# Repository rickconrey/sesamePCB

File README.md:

# Sesame PCB
The PCB for Sesame garage door opener

This PCB connects the [STM32F4Discovery](http://www.st.com/web/catalog/tools/FM116/SC959/SS1532/PF252419) board to the sparkfun [RN-52 breakout board](https://www.sparkfun.com/products/12849).

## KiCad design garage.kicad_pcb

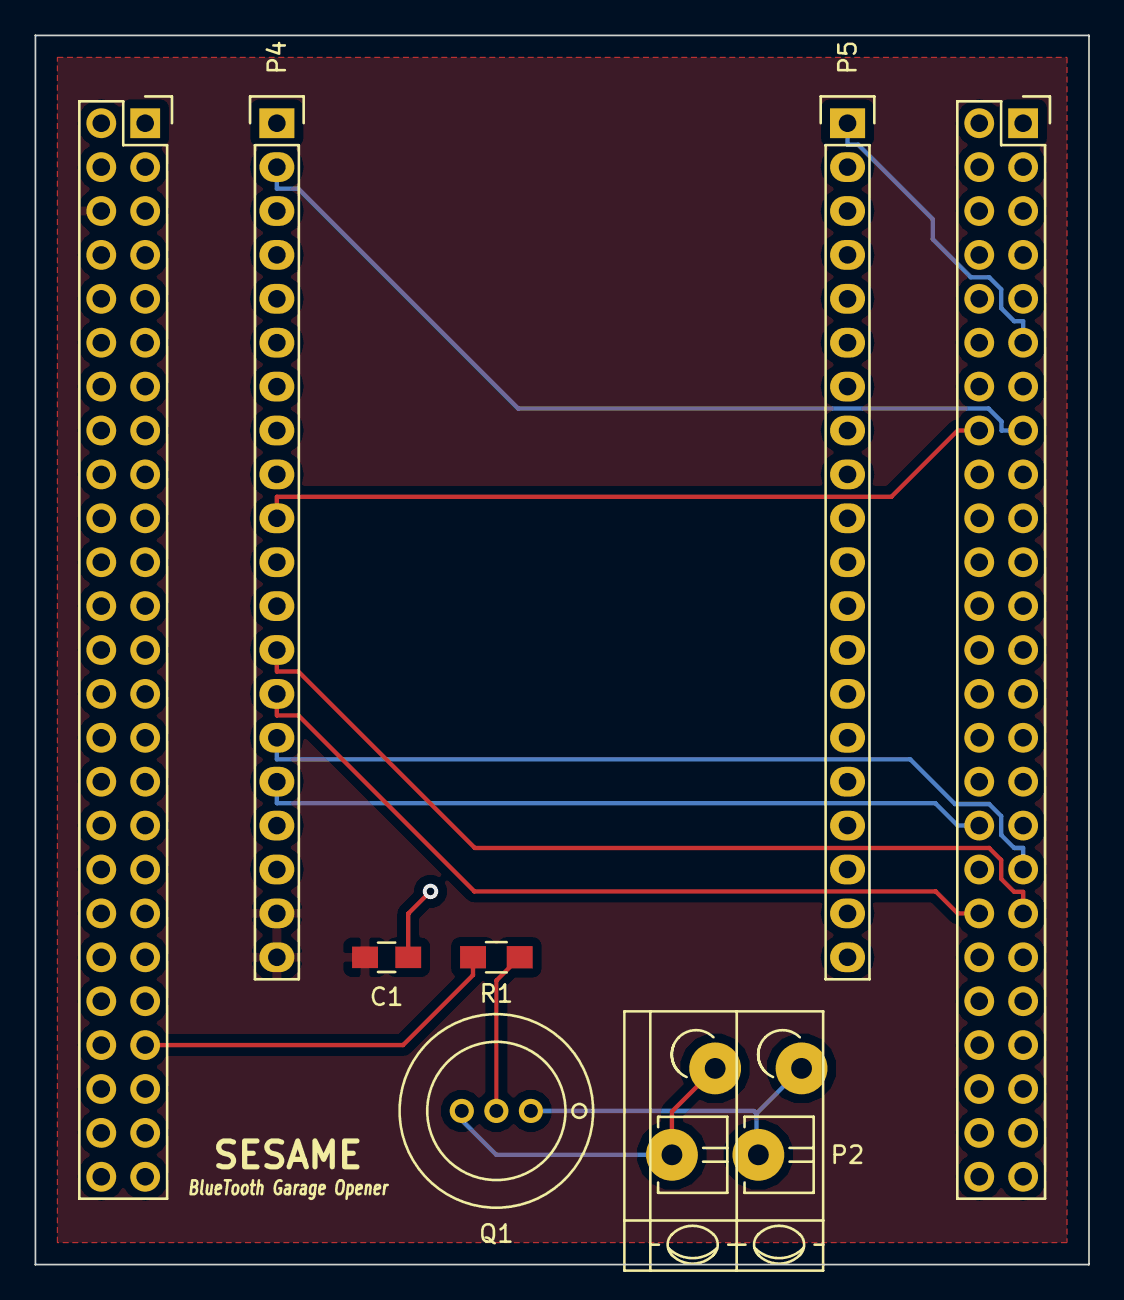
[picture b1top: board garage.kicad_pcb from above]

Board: 2 copper layers, 61.0 x 71.1 mm, 8 parts (0 on the bottom side), 12 nets.

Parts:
C1: 0.1u; C_0805_HandSoldering
P1, P3: CONN_02X25; Socket_Strip_Straight_2x25
P2: CONN_01X02; TerminalBlock_WAGO-804_RM5mm_2pol
P4, P5: CONN_01X20; Socket_Strip_Straight_1x20
Q1: 2N3904; OldSowjetaera_Transistor_Type-I_SmallPads
R1: 470; R_0805_HandSoldering

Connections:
3V: C1.1, P3.6, P4.19, P4.20
CTS: P1.38, P4.14
GND: C1.2, P2.2, P3.2, P5.20, Q1.1
GPIO2: P1.15, P4.2
GPIO9: P1.16, P4.10
Garage+: P2.1, Q1.3
unnamed: Q1.2, R1.1
PA1: P1.11, P5.1
PA8: P3.43, R1.2
RTS: P1.37, P4.13
RX: P1.34, P4.16
TX: P1.35, P4.15

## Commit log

2015-04-30 Initial commit.
2015-04-30 Added board outline
2015-04-30 Updated rules for OSH Park
2015-04-30 Reduced size of PCB by half
2015-05-01 Added ground plane
2015-05-01 Updated power and ground planes
2015-05-01 Added silkscreen
2015-05-01 Updated revision label
2015-05-01 Ignoring zip files
2015-05-01 Created gerber files
2015-05-01 updated labels
2015-05-26 added *.svg and *.plt
2015-05-26 Added ground to emitter of bjt. Switched pins 2 and 3 on bjt footprint.
2015-05-26 Changed traces to match schematic update.
2015-05-30 Removed R2
2015-05-30 Updated drill and gerber files
